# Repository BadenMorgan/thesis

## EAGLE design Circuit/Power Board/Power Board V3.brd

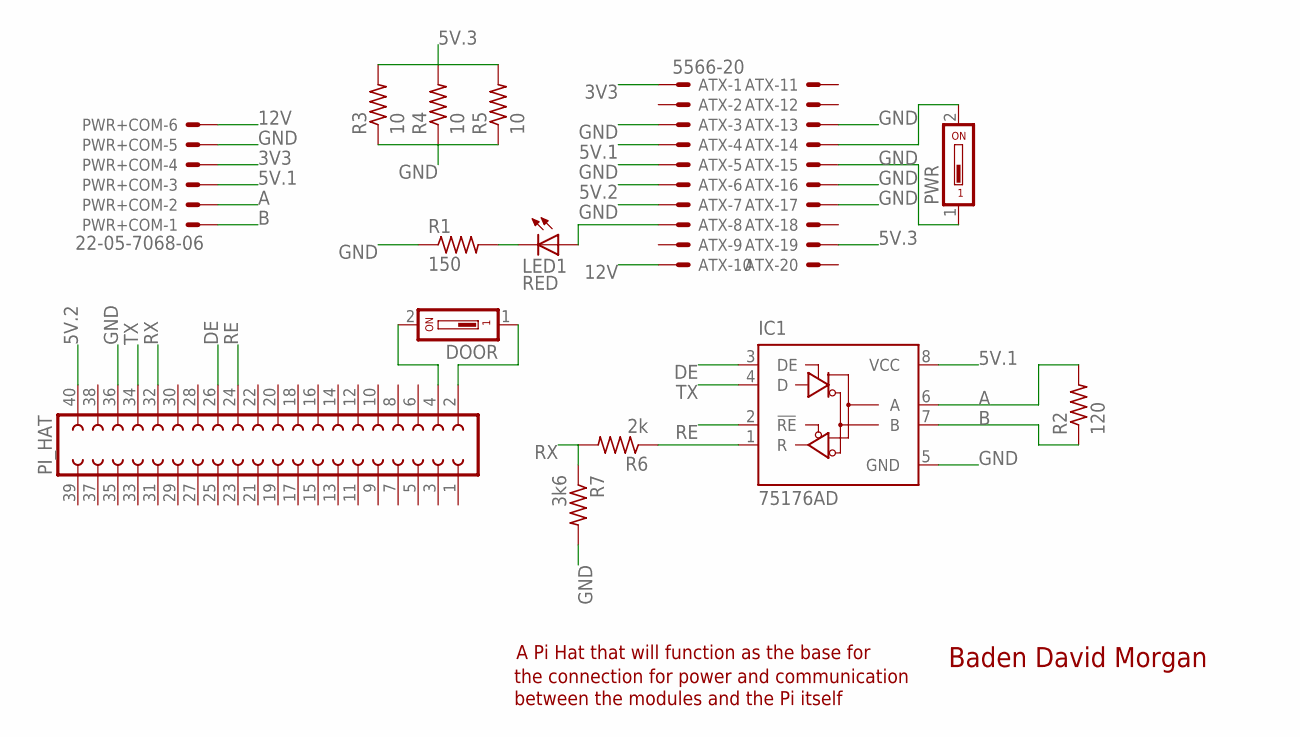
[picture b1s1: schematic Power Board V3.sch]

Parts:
ATX: 5566-20
DOOR: SD4-01
IC1: 75176AD; D_R-PDSO-G8
LED1: RED; CHIPLED_1206
PI_HAT: FE20-2
PWR: SD4-01
PWR+COM: 22-05-7068-06; 7395-06
R1: 150; R0805
R2: 120; R0805
R3, R4, R5: 10; P0817V
R6: 2k; R0805
R7: 3k6; R0805

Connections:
3V3: ATX.1, PWR+COM.4
5V.1: ATX.4, IC1.8 (VCC), PWR+COM.3
5V.2: ATX.6, PI_HAT.40
5V.3: ATX.19, R3.2, R4.2, R5.2
12V: ATX.10, PWR+COM.6
A: IC1.6 (A), PWR+COM.2, R2.2
B: IC1.7 (B), PWR+COM.1, R2.1
DE: IC1.3 (DE), PI_HAT.26
GND: ATX.3, ATX.5, ATX.7, ATX.13, ATX.15, ATX.16, ATX.17, IC1.5 (GND), PI_HAT.36, PWR.1, PWR+COM.5, R1.1, R3.1, R4.1, R5.1, R7.2
unnamed: ATX.14, PWR.2
unnamed: DOOR.2, PI_HAT.4
unnamed: ATX.8, LED1.A
unnamed: LED1.C, R1.2
unnamed: DOOR.1, PI_HAT.2
unnamed: IC1.1 (R), R6.1
RE: IC1.2 (!RE), PI_HAT.24
RX: PI_HAT.32, R6.2, R7.1
TX: IC1.4 (D), PI_HAT.34

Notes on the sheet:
Baden David Morgan
A Pi Hat that will function as the base for
the connection for power and communication
between the modules and the Pi itself

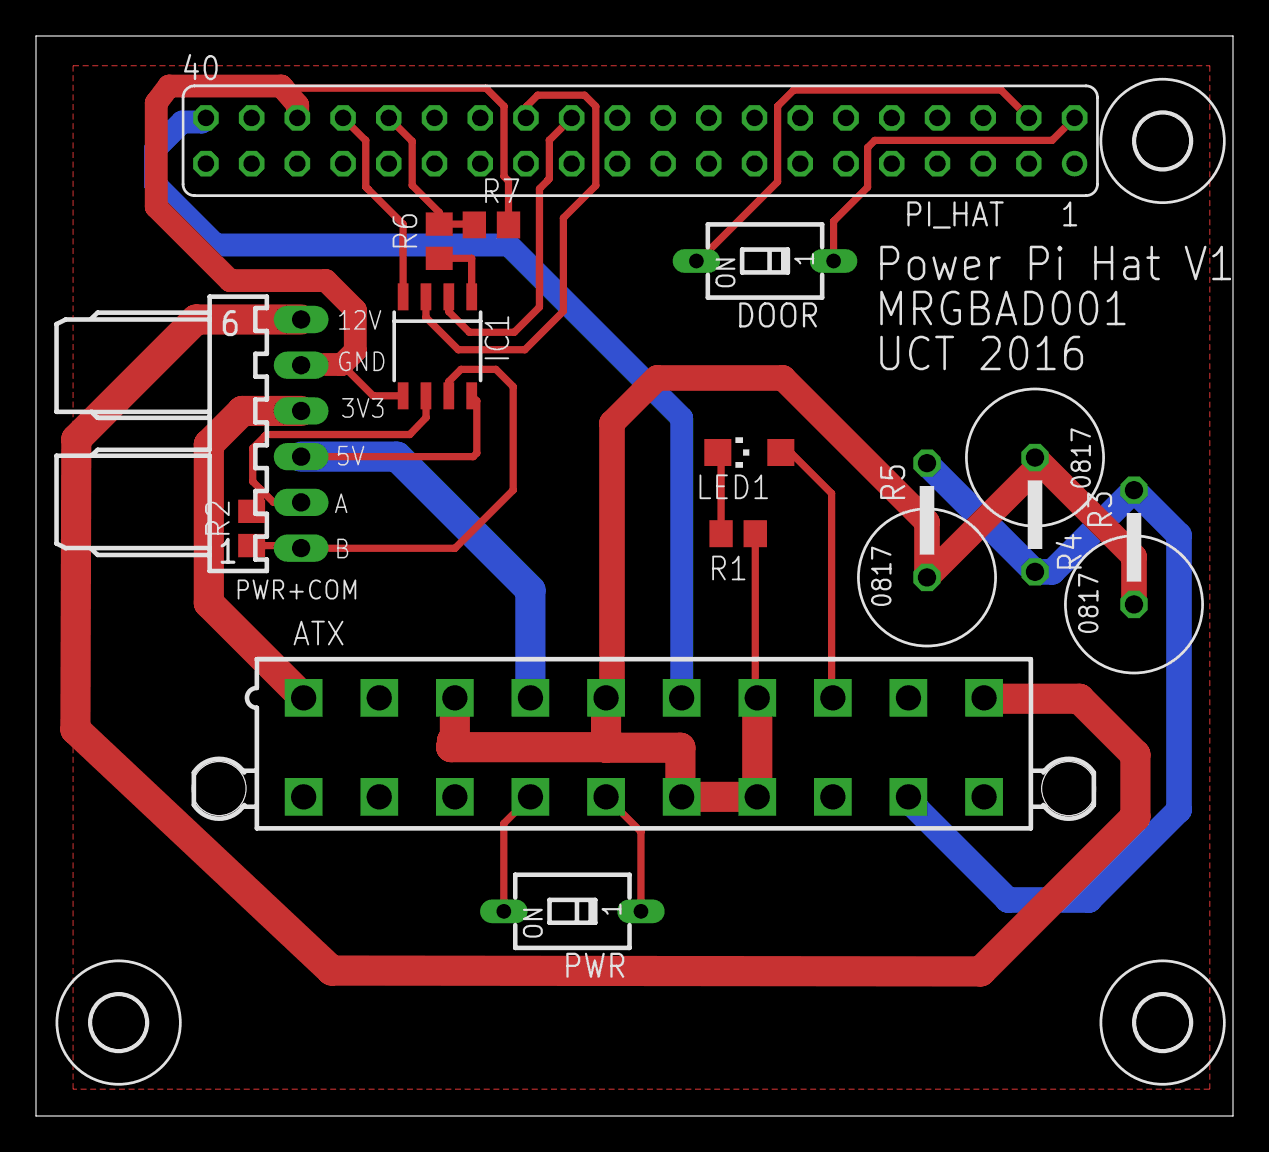
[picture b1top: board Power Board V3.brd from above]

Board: 2 copper layers, 66.5 x 60.0 mm, 17 parts (0 on the bottom side), 18 nets.

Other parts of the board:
U$1, U$2, U$3: 3,0

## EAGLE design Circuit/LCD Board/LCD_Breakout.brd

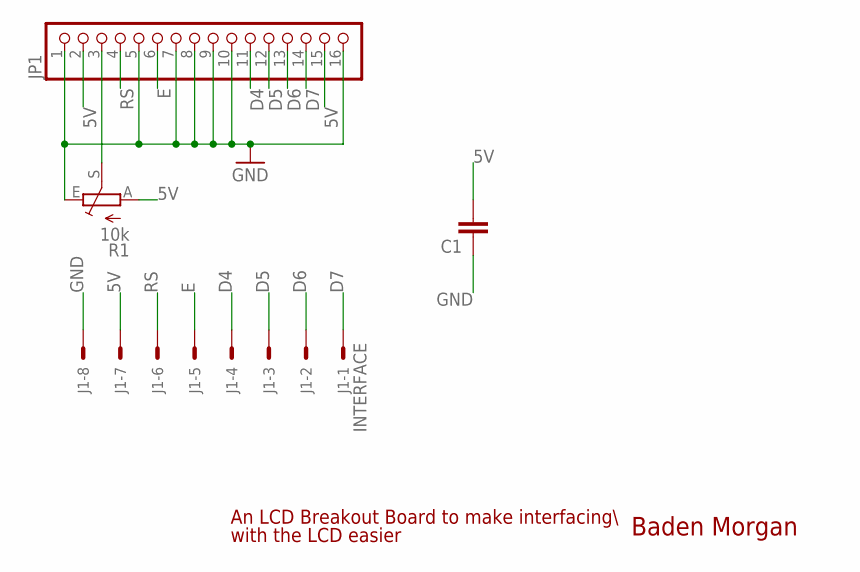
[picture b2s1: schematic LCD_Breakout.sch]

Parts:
C1: C5/2.5; C5B2.5
J1: INTERFACE; 7395-08
JP1: PINHD-1X16; 1X16
R1: 10k; CA6V

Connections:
5V: C1.2, J1.7, JP1.2, JP1.15, R1.A
D4: J1.4, JP1.11
D5: J1.3, JP1.12
D6: J1.2, JP1.13
D7: J1.1, JP1.14
E: J1.5, JP1.6
GND: C1.1, J1.8, JP1.1, JP1.5, JP1.7, JP1.8, JP1.9, JP1.10, JP1.16, R1.E
unnamed: JP1.3, R1.S
RS: J1.6, JP1.4

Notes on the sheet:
Baden Morgan
An LCD Breakout Board to make interfacing\
with the LCD easier

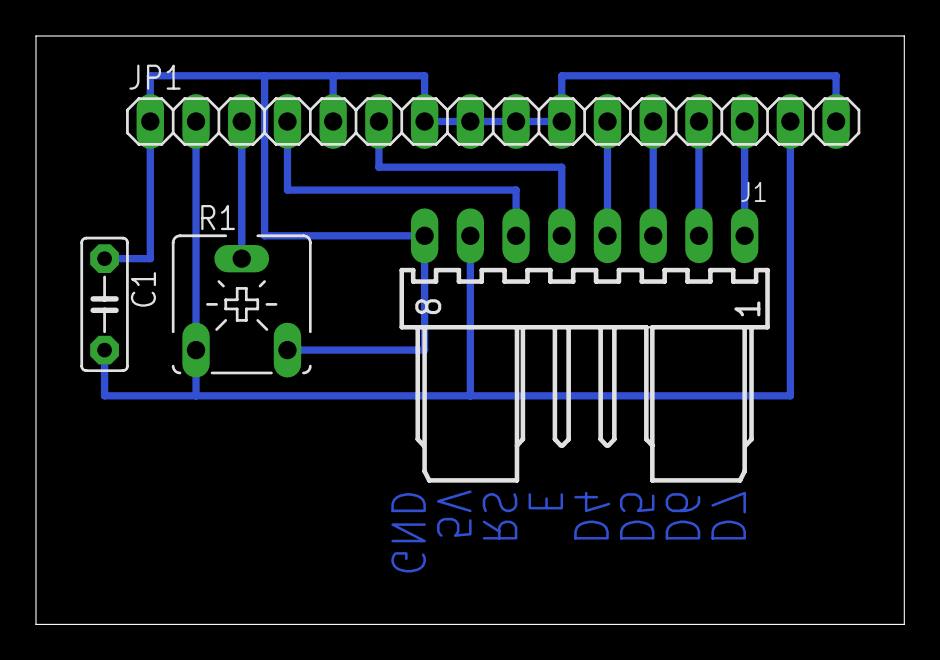
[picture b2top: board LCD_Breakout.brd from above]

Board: 2 copper layers, 48.2 x 32.7 mm, 4 parts (0 on the bottom side), 9 nets.

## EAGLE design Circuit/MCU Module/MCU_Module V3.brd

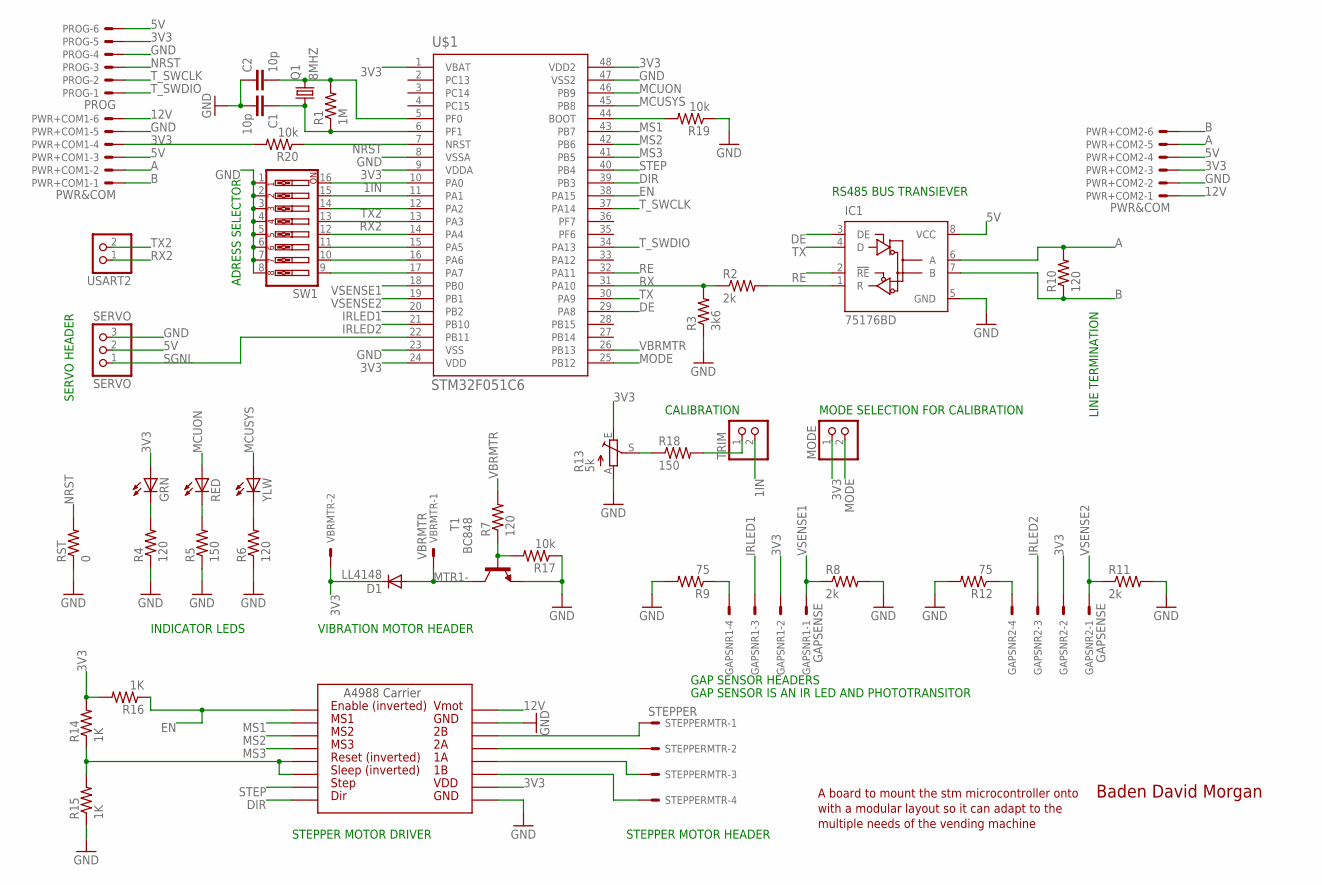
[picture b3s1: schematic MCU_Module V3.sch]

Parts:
C1, C2: 10p; C0805
D1: LL4148; SOD80C
GAPSNR1, GAPSNR2: GAPSENSE; 6410-04
GRN: LEDSML1206; SML1206
IC1: 75176BD; D_R-PDSO-G8
MODE: PINHD-1X2; 1X02
PROG: PROG; 6410-06
PWR+COM1, PWR+COM2: PWR&COM; 7395-06
Q1: 8MHZ; SM49
R1: 1M; R0805
R2, R8, R11: 2k; R0805
R3: 3k6; R0805
R4, R6, R7, R10: 120; R0805
R5, R18: 150; R0805
R9, R12: 75; R0805
R13: 5k; B25P
R14, R15, R16: 1K; R0805
R17, R19, R20: 10k; R0805
RED: LEDSML1206; SML1206
RST: 0; R0805
SERVO: SERVO; 1X03
STEPPERMTR: STEPPER; 6410-04
SW1: SW_DIP-8; EDG-08
T1: BC848; SOT23
TRIM: PINHD-1X2; 1X02
U$1: STM32F051C6; QFP50P900X900X160-48N
U$2: A4983CARRIER; A4988BREAKOUT
USART2: PINHD-1X2; 1X02
VBRMTR: VBRMTR; 6410-02
YLW: LEDSML1206; SML1206

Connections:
1IN: SW1.16, TRIM.2, U$1.10 (PA0)
3V3: D1.C, GAPSNR1.2, GAPSNR2.2, GRN.A, MODE.1, PROG.5, PWR+COM1.4, PWR+COM2.3, R13.E, R14.2, R16.2, R20.2, U$1.1 (VBAT), U$1.9 (VDDA), U$1.24 (VDD), U$1.48 (VDD2), U$2.VDD, VBRMTR.2
5V: IC1.8 (VCC), PROG.6, PWR+COM1.3, PWR+COM2.4, SERVO.2
8IN: SW1.9, U$1.17 (PA7)
12V: PWR+COM1.6, PWR+COM2.1, U$2.VMOT
A: IC1.6 (A), PWR+COM1.2, PWR+COM2.5, R10.2
B: IC1.7 (B), PWR+COM1.1, PWR+COM2.6, R10.1
DE: IC1.3 (DE), U$1.29 (PA8)
DIR: U$1.39 (PB3), U$2.DIR
EN: R16.1, U$1.38 (PA15), U$2.EN
GND: C1.2, C2.1, IC1.5 (GND), PROG.4, PWR+COM1.5, PWR+COM2.2, R3.1, R4.1, R5.1, R6.1, R8.2, R9.2, R11.2, R12.2, R13.A, R15.1, R17.1, R19.1, RST.1, SERVO.3, SW1.1, SW1.2, SW1.3, SW1.4, SW1.5, SW1.6, SW1.7, SW1.8, T1.2 (E), U$1.8 (VSSA), U$1.23 (VSS), U$1.47 (VSS2), U$2.GND, U$2.GND@0 (GND)
IRLED1: GAPSNR1.3, U$1.20 (PB2)
IRLED2: GAPSNR2.3, U$1.21 (PB10)
MCUON: RED.A, U$1.46 (PB9)
MCUSYS: U$1.45 (PB8), YLW.A
MODE: MODE.2, U$1.25 (PB12)
MS1: U$1.43 (PB7), U$2.MS1
MS2: U$1.42 (PB6), U$2.MS2
MS3: U$1.41 (PB5), U$2.MS3
MTR1-: D1.A, T1.3 (C), VBRMTR.1
unnamed: C1.1, Q1.1, R1.1, U$1.6 (PF1)
unnamed: C2.2, Q1.2, R1.2, U$1.5 (PF0)
unnamed: STEPPERMTR.4, U$2.1B
unnamed: SW1.15, U$1.11 (PA1)
unnamed: IC1.1 (R), R2.2
unnamed: SW1.12, U$1.14 (PA4)
unnamed: SW1.11, U$1.15 (PA5)
unnamed: SW1.10, U$1.16 (PA6)
unnamed: R13.S, R18.1
unnamed: GRN.C, R4.2
unnamed: R5.2, RED.C
unnamed: R6.2, YLW.C
unnamed: R7.1, R17.2, T1.1 (B)
unnamed: STEPPERMTR.3, U$2.1A
unnamed: GAPSNR1.4, R9.1
unnamed: STEPPERMTR.2, U$2.2A
unnamed: STEPPERMTR.1, U$2.2B
unnamed: R19.2, U$1.44 (BOOT)
unnamed: R18.2, TRIM.1
unnamed: GAPSNR2.4, R12.1
unnamed: R14.1, R15.2, U$2.RST, U$2.SLP (SLEEP)
NRST: PROG.3, R20.1, RST.2, U$1.7 (NRST)
RE: IC1.2 (!RE), U$1.32 (PA11)
RX: R2.1, R3.2, U$1.31 (PA10)
RX2: SW1.13, U$1.13 (PA3), USART2.1
SGNL: SERVO.1, U$1.22 (PB11)
STEP: U$1.40 (PB4), U$2.STEP
TX: IC1.4 (D), U$1.30 (PA9)
TX2: SW1.14, U$1.12 (PA2), USART2.2
T_SWCLK: PROG.2, U$1.37 (PA14)
T_SWDIO: PROG.1, U$1.34 (PA13)
VBRMTR: R7.2, U$1.26 (PB13)
VSENSE1: GAPSNR1.1, R8.1, U$1.18 (PB0)
VSENSE2: GAPSNR2.1, R11.1, U$1.19 (PB1)

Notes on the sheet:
A board to mount the stm microcontroller onto
with a modular layout so it can adapt to the
multiple needs of the vending machine
Baden David Morgan
RS485 BUS TRANSIEVER
SERVO HEADER
VIBRATION MOTOR HEADER
INDICATOR LEDS
ADRESS SELECTOR
GAP SENSOR HEADERS
GAP SENSOR IS AN IR LED AND PHOTOTRANSITOR
LINE TERMINATION
STEPPER MOTOR DRIVER
STEPPER MOTOR HEADER
MODE SELECTION FOR CALIBRATION
CALIBRATION

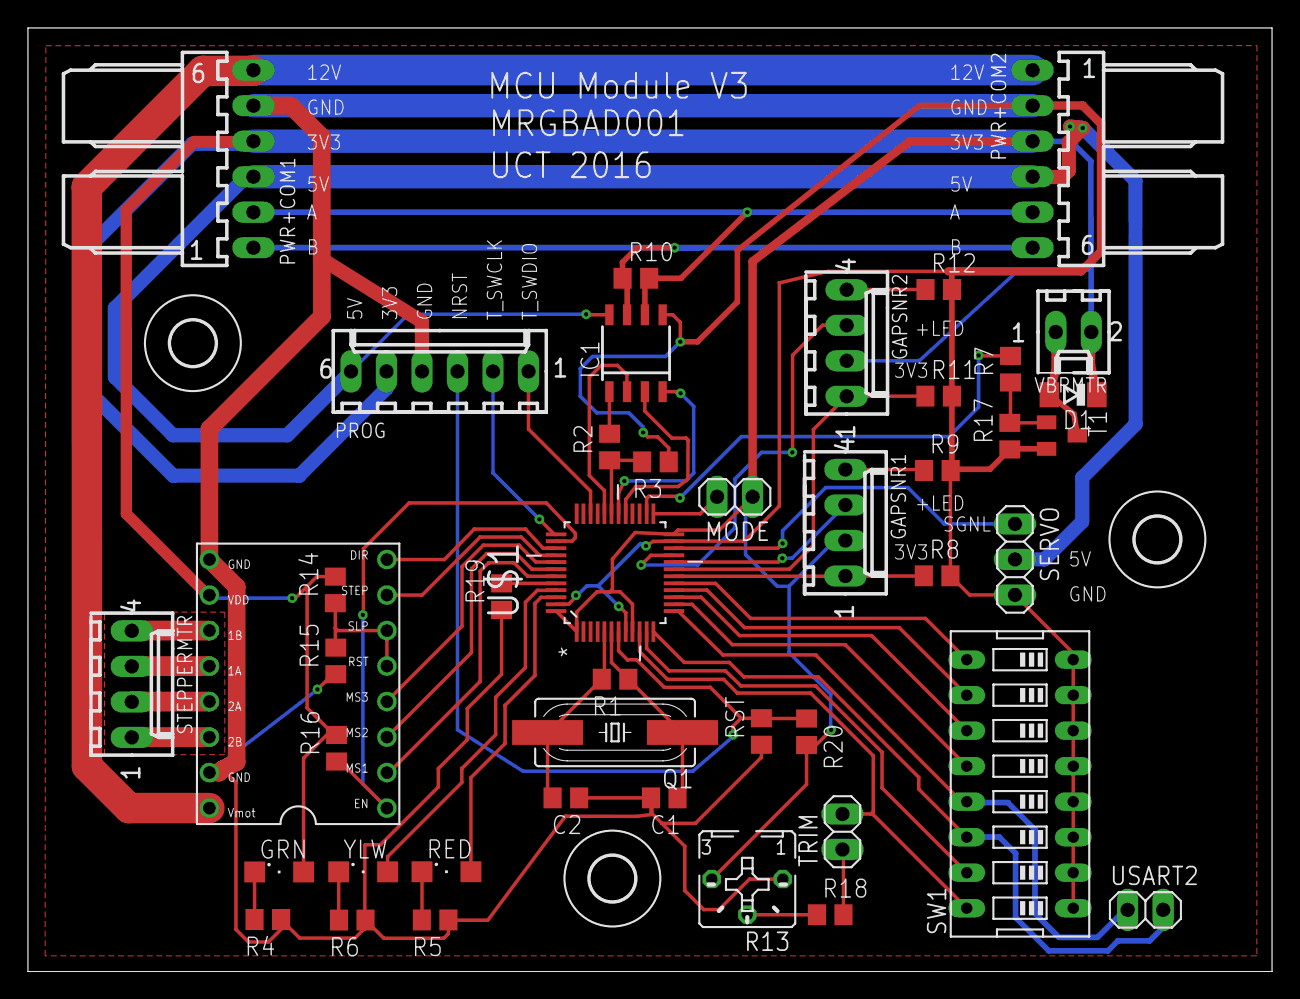
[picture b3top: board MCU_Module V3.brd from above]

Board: 2 copper layers, 89.0 x 67.5 mm, 47 parts (0 on the bottom side), 54 nets.

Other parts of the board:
U$3, U$4, U$5: 3,2

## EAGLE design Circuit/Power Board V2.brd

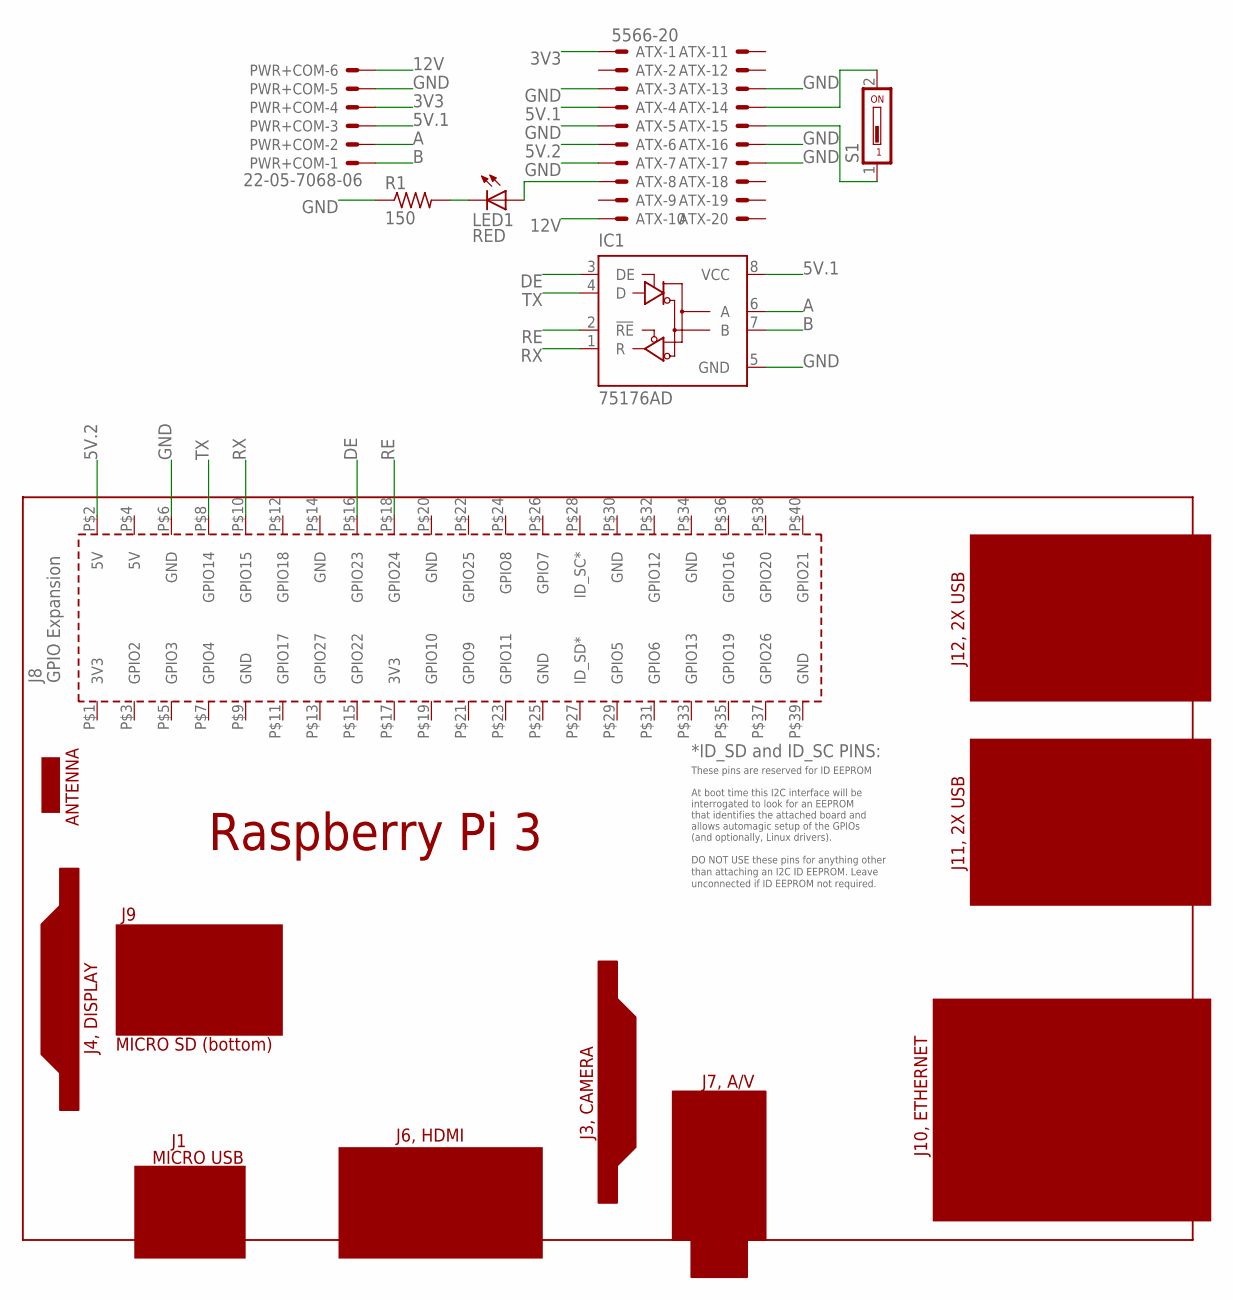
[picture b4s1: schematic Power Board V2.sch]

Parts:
ATX: 5566-20
IC1: 75176AD; D_R-PDSO-G8
LED1: RED; CHIPLED_1206
PCB1: RPI3
PWR+COM: 22-05-7068-06; 7395-06
R1: 150; R0805
S1: SD4-01

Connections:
3V3: ATX.1, PWR+COM.4
5V.1: ATX.4, IC1.8 (VCC), PWR+COM.3
5V.2: ATX.6, PCB1.P$2 (5V)
12V: ATX.10, PWR+COM.6
A: IC1.6 (A), PWR+COM.2
B: IC1.7 (B), PWR+COM.1
DE: IC1.3 (DE), PCB1.P$16 (GPIO23)
GND: ATX.3, ATX.5, ATX.7, ATX.13, ATX.16, ATX.17, IC1.5 (GND), PCB1.P$6 (GND), PWR+COM.5, R1.1
unnamed: ATX.14, S1.2
unnamed: ATX.15, S1.1
unnamed: ATX.8, LED1.A
unnamed: LED1.C, R1.2
RE: IC1.2 (!RE), PCB1.P$18 (GPIO24)
RX: IC1.1 (R), PCB1.P$10 (GPIO15)
TX: IC1.4 (D), PCB1.P$8 (GPIO14)

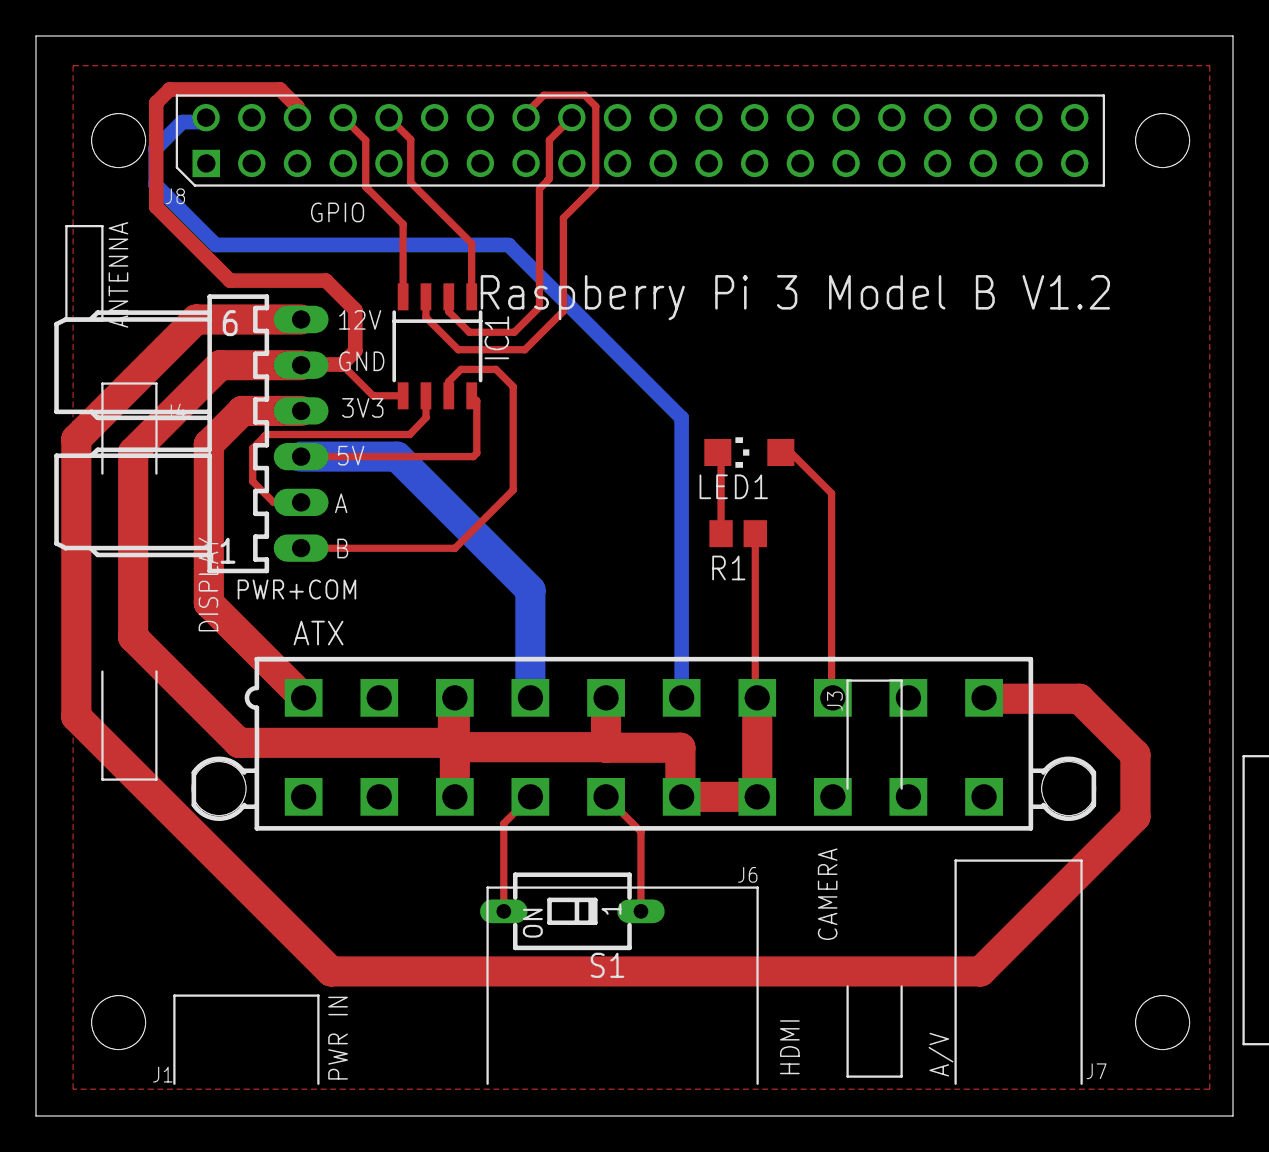
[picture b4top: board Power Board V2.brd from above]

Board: 2 copper layers, 66.5 x 60.0 mm, 7 parts (0 on the bottom side), 15 nets.

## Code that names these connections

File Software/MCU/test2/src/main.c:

#define STM32F051

#include <stdint.h>
#include "stm32f0xx.h"

// This projects demonstrates PWM on the RG LED
// Red:   PB10, TIM2_CH3
// Green: PB11, TIM2_CH4
// Both run on AF2

void init_timer(void);
void init_leds(void);

void init_adc(void);


void main(void) {
    uint32_t delay_cnt;
  init_timer();
  init_leds();
  init_adc();
  while(1){
          // start conversion
    ADC1->CR |= ADC_CR_ADSTART;
    // wait for end of conversion: EOC == 1. Not necessary to clear EOC as we read from DR
    while((ADC1->ISR & ADC_ISR_EOC) == 0);
    //for(delay_cnt = 0; delay_cnt < 1000000; ++delay_cnt);
    uint8_t adcval = ADC1->DR;
    GPIOB->ODR = adcval;
    uint8_t percentage = adcval/3;
    TIM2->CCR4 = percentage * 80; // Green = 90%
  }
}

void init_timer(void) {
  RCC->AHBENR |= RCC_AHBENR_GPIOBEN;
  RCC->APB1ENR |= RCC_APB1ENR_TIM2EN;

  GPIOB->MODER |= GPIO_MODER_MODER10_1; // PB10 = AF
  GPIOB->MODER |= GPIO_MODER_MODER11_1; // PB11 = AF
  GPIOB->AFR[1] |= (2 << (4*(10 - 8))); // PB10_AF = AF2 (ie: map to TIM2_CH3)
  GPIOB->AFR[1] |= (2 << (4*(11 - 8))); // PB11_AF = AF2 (ie: map to TIM2_CH4)

  TIM2->ARR = 8000;  // f = 1 KHz
  // specify PWM mode: OCxM bits in CCMRx. We want mode 1
  TIM2->CCMR2 |= (TIM_CCMR2_OC3M_2 | TIM_CCMR2_OC3M_1); // PWM Mode 1
  TIM2->CCMR2 |= (TIM_CCMR2_OC4M_2 | TIM_CCMR2_OC4M_1); // PWM Mode 1
  // set PWM percantages
  TIM2->CCR3 = 20 * 80; // Red = 20%
  TIM2->CCR4 = 90 * 80; // Green = 90%

  // enable the OC channels
  TIM2->CCER |= TIM_CCER_CC3E;
  TIM2->CCER |= TIM_CCER_CC4E;

  TIM2->CR1 |= TIM_CR1_CEN; // counter enable
}

void init_leds(void) {
  RCC->AHBENR |= RCC_AHBENR_GPIOBEN;   //enable clock for LEDs
  GPIOB->MODER |= GPIO_MODER_MODER0_0; //set PB0 to output
  GPIOB->MODER |= GPIO_MODER_MODER1_0; //set PB1 to output
  GPIOB->MODER |= GPIO_MODER_MODER2_0; //set PB2 to output
  GPIOB->MODER |= GPIO_MODER_MODER3_0; //set PB3 to output
  GPIOB->MODER |= GPIO_MODER_MODER4_0; //set PB4 to output
  GPIOB->MODER |= GPIO_MODER_MODER5_0; //set PB5 to output
  GPIOB->MODER |= GPIO_MODER_MODER6_0; //set PB6 to output
  GPIOB->MODER |= GPIO_MODER_MODER7_0; //set PB7 to output
  GPIOB->MODER |= GPIO_MODER_MODER8_0; //set PB7 to output
  GPIOB->MODER |= GPIO_MODER_MODER9_0; //set PB7 to output
  GPIO_INIT()

}

void init_adc(void) {
  RCC->APB2ENR |= RCC_APB2ENR_ADCEN; //enable clock for ADC
  RCC->AHBENR |= RCC_AHBENR_GPIOAEN; //enable clock for port which ADC samples from
  GPIOA->MODER |= GPIO_MODER_MODER5; //set PA5 to analogue mode
  ADC1->CHSELR |= ADC_CHSELR_CHSEL5; // select channel 5
  ADC1->CFGR1 |= ADC_CFGR1_RES_1;    // resolution to 8 bit
  ADC1->CR |= ADC_CR_ADCAL;         // set ADCAL high and wait for it to go low
  while( (ADC1->CR & ADC_CR_ADCAL) != 0);
  ADC1->CR |= ADC_CR_ADEN;           // set ADEN=1 in the ADC_CR register
  while((ADC1->ISR & ADC_ISR_ADRDY) == 0); //wait until ADRDY==1 in ADC_ISR
}

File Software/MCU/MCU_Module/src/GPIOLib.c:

#include "GPIOLib.h"


/*
setup of the GPIO for on led, status led, vibration motor,
irled 1 and 2, mode selection, re and de, ms 1,2 & 3,
step direction and enable
*/

//set up GPIO as input/output
void GPIOInit(){
    GPIO_InitTypeDef GPIO_InitStructure;

    RCC_AHBPeriphClockCmd(RCC_AHBPeriph_GPIOB, ENABLE);
    RCC_AHBPeriphClockCmd(RCC_AHBPeriph_GPIOA, ENABLE);

    //MCUON Output
    GPIO_InitStructure.GPIO_Pin = MCUON;
    GPIO_InitStructure.GPIO_Mode = GPIO_Mode_OUT;
    GPIO_Init(GPIOB, &GPIO_InitStructure);
    GPIO_WriteBit(GPIOB,MCUON,1);
    //MCUStatus Output
    GPIO_InitStructure.GPIO_Pin = MCUSYS;
    GPIO_InitStructure.GPIO_Mode = GPIO_Mode_OUT;
    GPIO_Init(GPIOB, &GPIO_InitStructure);
    GPIO_WriteBit(GPIOB,MCUSYS,1);
    //IRLED1
    GPIO_InitStructure.GPIO_Pin = IRLED1;
    GPIO_InitStructure.GPIO_Mode = GPIO_Mode_OUT;
    GPIO_Init(GPIOB, &GPIO_InitStructure);
    GPIO_WriteBit(GPIOB,IRLED1,0);
    //IRLED2
    GPIO_InitStructure.GPIO_Pin = IRLED2;
    GPIO_InitStructure.GPIO_Mode = GPIO_Mode_OUT;
    GPIO_Init(GPIOB, &GPIO_InitStructure);
    GPIO_WriteBit(GPIOB,IRLED2,0);
    //MODE
    GPIO_InitStructure.GPIO_Pin = MODE;
    GPIO_InitStructure.GPIO_Mode = GPIO_Mode_IN;
    GPIO_InitStructure.GPIO_PuPd = GPIO_PuPd_DOWN;
    GPIO_Init(GPIOB, &GPIO_InitStructure);
    //VBRMTR
    GPIO_InitStructure.GPIO_Pin = VBRMTR;
    GPIO_InitStructure.GPIO_Mode = GPIO_Mode_OUT;
    GPIO_Init(GPIOB, &GPIO_InitStructure);
    GPIO_WriteBit(GPIOB,VBRMTR,0);
    //DE
    GPIO_InitStructure.GPIO_Pin = DE;
    GPIO_InitStructure.GPIO_Mode = GPIO_Mode_OUT;
    GPIO_Init(GPIOA, &GPIO_InitStructure);
    GPIO_WriteBit(GPIOA,DE,0);
    //RE
    GPIO_InitStructure.GPIO_Pin = RE;
    GPIO_InitStructure.GPIO_Mode = GPIO_Mode_OUT;
    GPIO_Init(GPIOA, &GPIO_InitStructure);
    GPIO_WriteBit(GPIOA,RE,0);
}

//ADRESS setup
uint8_t InitAdress(){
    GPIO_InitTypeDef GPIO_InitStructure;
    //bit 0
    GPIO_InitStructure.GPIO_Pin = GPIO_Pin_0;
    GPIO_InitStructure.GPIO_Mode = GPIO_Mode_IN;
    GPIO_InitStructure.GPIO_PuPd = GPIO_PuPd_UP;
    GPIO_Init(GPIOA, &GPIO_InitStructure);
    //bit 1
    GPIO_InitStructure.GPIO_Pin = GPIO_Pin_1;
    GPIO_InitStructure.GPIO_Mode = GPIO_Mode_IN;
    GPIO_InitStructure.GPIO_PuPd = GPIO_PuPd_UP;
    GPIO_Init(GPIOA, &GPIO_InitStructure);
    //bit 2
    GPIO_InitStructure.GPIO_Pin = GPIO_Pin_2;
    GPIO_InitStructure.GPIO_Mode = GPIO_Mode_IN;
    GPIO_InitStructure.GPIO_PuPd = GPIO_PuPd_UP;
    GPIO_Init(GPIOA, &GPIO_InitStructure);
    //bit 3
    GPIO_InitStructure.GPIO_Pin = GPIO_Pin_3;
    GPIO_InitStructure.GPIO_Mode = GPIO_Mode_IN;
    GPIO_InitStructure.GPIO_PuPd = GPIO_PuPd_UP;
    GPIO_Init(GPIOA, &GPIO_InitStructure);
    //bit 4
    GPIO_InitStructure.GPIO_Pin = GPIO_Pin_4;
    GPIO_InitStructure.GPIO_Mode = GPIO_Mode_IN;
    GPIO_InitStructure.GPIO_PuPd = GPIO_PuPd_UP;
    GPIO_Init(GPIOA, &GPIO_InitStructure);
    //bit 5
    GPIO_InitStructure.GPIO_Pin = GPIO_Pin_5;
    GPIO_InitStructure.GPIO_Mode = GPIO_Mode_IN;
    GPIO_InitStructure.GPIO_PuPd = GPIO_PuPd_UP;
    GPIO_Init(GPIOA, &GPIO_InitStructure);
    //bit 6
    GPIO_InitStructure.GPIO_Pin = GPIO_Pin_6;
    GPIO_InitStructure.GPIO_Mode = GPIO_Mode_IN;
    GPIO_InitStructure.GPIO_PuPd = GPIO_PuPd_UP;
    GPIO_Init(GPIOA, &GPIO_InitStructure);
    //bit 7
    GPIO_InitStructure.GPIO_Pin = GPIO_Pin_7;
    GPIO_InitStructure.GPIO_Mode = GPIO_Mode_IN;
    GPIO_InitStructure.GPIO_PuPd = GPIO_PuPd_UP;
    GPIO_Init(GPIOA, &GPIO_InitStructure);

    uint16_t pinread = GPIO_ReadInputData(GPIOA);
    uint64_t NewAddress = pinread & 0xFF;
    return NewAddress^0xFF;
}

//initialize 3 adc's for vsense1, vsense2 and alignment
void ADCsInit(){
    RCC->APB2ENR |= RCC_APB2ENR_ADCEN; //enable clock for ADC
    //clock already enabled
    GPIOA->MODER |= GPIO_MODER_MODER0; //set PA0 to analogue mode
    GPIOB->MODER |= GPIO_MODER_MODER0; //set PB0 to analogue mode
    GPIOB->MODER |= GPIO_MODER_MODER1; //set PB1 to analogue mode

    ADC1->CR |= ADC_CR_ADCAL;         // set ADCAL high and wait for it to go low
    while( (ADC1->CR & ADC_CR_ADCAL) != 0);
    ADC1->CR |= ADC_CR_ADEN;           // set ADEN=1 in the ADC_CR register
    while((ADC1->ISR & ADC_ISR_ADRDY) == 0); //wait until ADRDY==1 in ADC_ISR

    ADC1->CHSELR |= ADC_CHSELR_CHSEL9; // select channel 8
    ADC1->CFGR1 |= ADC_CFGR1_RES_1;    // resolution to 8 bit
}

//fetch requested ADC value
uint8_t GetADCVal(uint8_t Channel){
    if(Channel == channel0){
        ADC1->CHSELR = ADC_CHSELR_CHSEL0; // select channel 0
    }else if(Channel == channel8){
        ADC1->CHSELR = ADC_CHSELR_CHSEL8; // select channel 8
    }else if(Channel == channel9){
        ADC1->CHSELR = ADC_CHSELR_CHSEL9; // select channel 9
    }

    ADC1->CR |= ADC_CR_ADSTART;
    // wait for end of conversion: EOC == 1. Not necessary to clear EOC as we read from DR
    while((ADC1->ISR & ADC_ISR_EOC) == 0);
    return ADC1->DR;
}

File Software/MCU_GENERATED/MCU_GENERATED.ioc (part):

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Mcu.Name=STM32F051C6Tx
Mcu.Package=LQFP48
Mcu.UserName=STM32F051C6Tx
PA0.Mode=IN0
PA0.Signal=ADC_IN0
PA10.Mode=Asynchronous
PA10.Signal=USART1_RX
PA2.Mode=Asynchronous
PA2.Signal=USART2_TX
PA3.Mode=Asynchronous
PA3.Signal=USART2_RX
PA9.Mode=Asynchronous
PA9.Signal=USART1_TX
PB0.Mode=IN8
PB0.Signal=ADC_IN8
PB1.Mode=IN9
PB1.Signal=ADC_IN9
board=MCU_GENERATED

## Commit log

2016-07-02 :octocat: Added .gitattributes & .gitignore files
2016-07-02 creating repo
2016-07-18 adding more files
    topic description
2016-07-18 added cmap
2016-07-18 additions to cmap
2016-07-25 updated Cmap and gantt chart
2016-07-26 added document
    *initializations
    *cover page
    *plagiarism declaration
2016-07-26 adding schematic
2016-07-26 deleting old named file
2016-07-30 updated schematic started on relearning stm32f0
2016-08-04 completed delivery idea 1 and progress on circuit
    *finished first draft of delivery idea 1
    *started delivery idea 2
    *made progress on circuit
    *finished schematic
    *half way through layout
2016-08-04 removing temporary files
2016-08-10 redid layout and updated document
    updated the document and redid the layout to improve layout and added
    more initilizaton to the document
2016-08-14 finished circuit
    finished circuit board and added gerber files
    setting up for roller 2 version 2
2016-08-19 added website and started stm code
    website foreground mostly done
    started with st code
2016-08-23 updates
    *updated power board to added voltage devider for pi coms
    *updated solidworks drawings and parts for bigger servo
    *updated MCU porgam, to many to list fully, brief is gpio, task manager,
    servo, timer, usarts
2016-08-24 updates
    *added datasheets to the webstie
    *added LCD breakout board
    *updated report
    *updated task manager in micro program
2016-08-25 finished main task for mcu
2016-08-25 added serial monitor receiver handler
2016-08-29 updates
    updated 3d prints to optimize for priting
    widdened slot to add adjustable guide
    connected pi to stm via uart
    added interrupt for uart1 stm
    setup aurt on pi
2016-08-29 updates
    final edition for contacts page done
    added detaled alert
    python script now connect to mysql database to fetch address to send to
2016-09-05 couple updates
2016-09-09 many updates
    *added to the doc
    *updated stm code to send response codes
    *added handling on master side for repsonse codes
    *added functionality so coms will work with rs485 bus transiever
    *master giving user friendly response after dispensing
2016-09-14 updates
    *impleted log system for master program
    *added a component check that makes sure there are a specific number of
    orders in the database for an indavidual student, checks on ordering to
    make it so it is an order level operation and cant be overriden by
    manipulating the database
    *made it so orders only allow limited number of components now
2016-09-16 u[date for making enclosure
2016-09-21 updates
    Mostly to document ith some additions of drawings from solidworks for
    the document
    Also the 9g servo for the updated delivery mechanism was replaced with
    one that reprsents the real life one more closely
2016-10-07 lots of updates
    too many to document I've been a lazy uploader
2016-10-17 Document updates
2016-10-31 document updates
    sorry its been a while
2016-11-01 added boot time scripting file
2016-11-02 Mainly document updates
    *recommendations
    *intro
    *more assembly proccess'
    * more
2016-11-03 updates master program
    changed back to rfid activation
2016-11-05 fixed serial problems
2016-11-06 started applying language edits
2016-11-08 oh the comits
2016-11-10 document proof reading updates
2016-11-11 updates on document
2016-11-13 Document Updates
    lots of edits
2016-11-13 more updates for final release
2016-11-13 more proof reading updates
2016-11-13 major update vmmaster and proof reading
    vmmaster for final version and proof reading additions
2016-11-14 for submittion almost
    will probably need some cleaning up
2016-12-01 presentation upload
2016-12-05 update
    bug fixes
2016-12-07 update mcy module to latest
    bug fixes
2016-12-07 donno what this is
2017-02-14 could be anything
